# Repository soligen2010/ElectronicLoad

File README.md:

# ElectronicLoad

Here is my DC Load project, inspired by Dave Jones, MJLorton, and Kibi.

I have this on a breadboard and it all seems to be working, but as I am a beginner, I would appreciate any feedback before I start soldering.

I built in an Arduino and 16 bit DAC (ADS1115) to monitor and display volts and amps without a multi meter. It also displays watts, and software enforces max watts. It will turn off the load if the watts or voltage exceeds the software limits.

Several break-out boards are referenced: Arduino Nano, 16x2 LCD, ADS1115, and my own negative 2.5 volt generator. I don’t have the schematic drawn for the -2.5 generator. Basically the PWM drives a totem pole and capacitors/diodes to get the negative voltage, then regulated with a TL431A. Even though the TLC272 is supposed to go to ground, I found it wasn’t very good near ground, so I added the negative. I probably only needed -.5V, but -2.5V is the TL431 reference voltage.

Power is supplied by an old camera battery charger that I hacked into a DC supply. I figure anything at around 9V should work fine. The heat sink fan is the only thing driven directly by the input voltage. Everything else either uses the Arduino’s built in 5V regulator or 7.5V regulated by VR1.

Output from IC1A is split with identical voltage dividers – one to set the input to IC1B and the other goes to the DAC for reading by the Arduino.

Q2 is Arduino controlled and turns the load on or off. R13 ensures the output of IC1B is low when the load is off by pulling the non-inverting input down to about -.6V. The LCD display will show either the “set” amps or the actual amps depending if it is in “set” or “run” mode (controlled by MODE_BUTTON).

Q3 is an HRF3205 that I salvaged from an old UPS. I had started out using an FQP30N06, but I fried several, so went to the HRF3205 which handles a lot more current. The only theory I have for FQP30N06 is the amp surge when the load turns on. I did a re-design to reduce the turn on surge time by making sure IC1B output is LOW when the load is off (Q2 and R13). But I still went with the HRF3205.

Stabilizing the feedback was my biggest challenge. I wish I would have bought an oscilloscope sooner . When I changed to the HRF3205, I had to change C4 from 10n to 100n, added R14 (and R5 for symmetry) and removed the 100R resistor I had between IC1B and Q3. C4 ended up bigger than I expected it should be, and I am a bit uncertain about the lack of a Q3 gate resistor, so comments on this are welcome.

I didn’t fully buffer the inputs to the DAC. When I had put them in, the buffer added error, so I decided to remove them to simplify the circuit and compensate for the low impedance DAC inputs in software. The software will handle all calibration and compensation for any mis-matched component values.

I tested with various amp settings at 3.3ish, 5ish, and 12ish volts using a converted ATX power supply. I also testing the low end with an AA cell that I abusively drained. I’d like to test with some higher voltages to see how it does, but first I’ll need to build something that can go higher than 12V.

 Copyright 2018 by Dennis Cabell
 KE8FZX

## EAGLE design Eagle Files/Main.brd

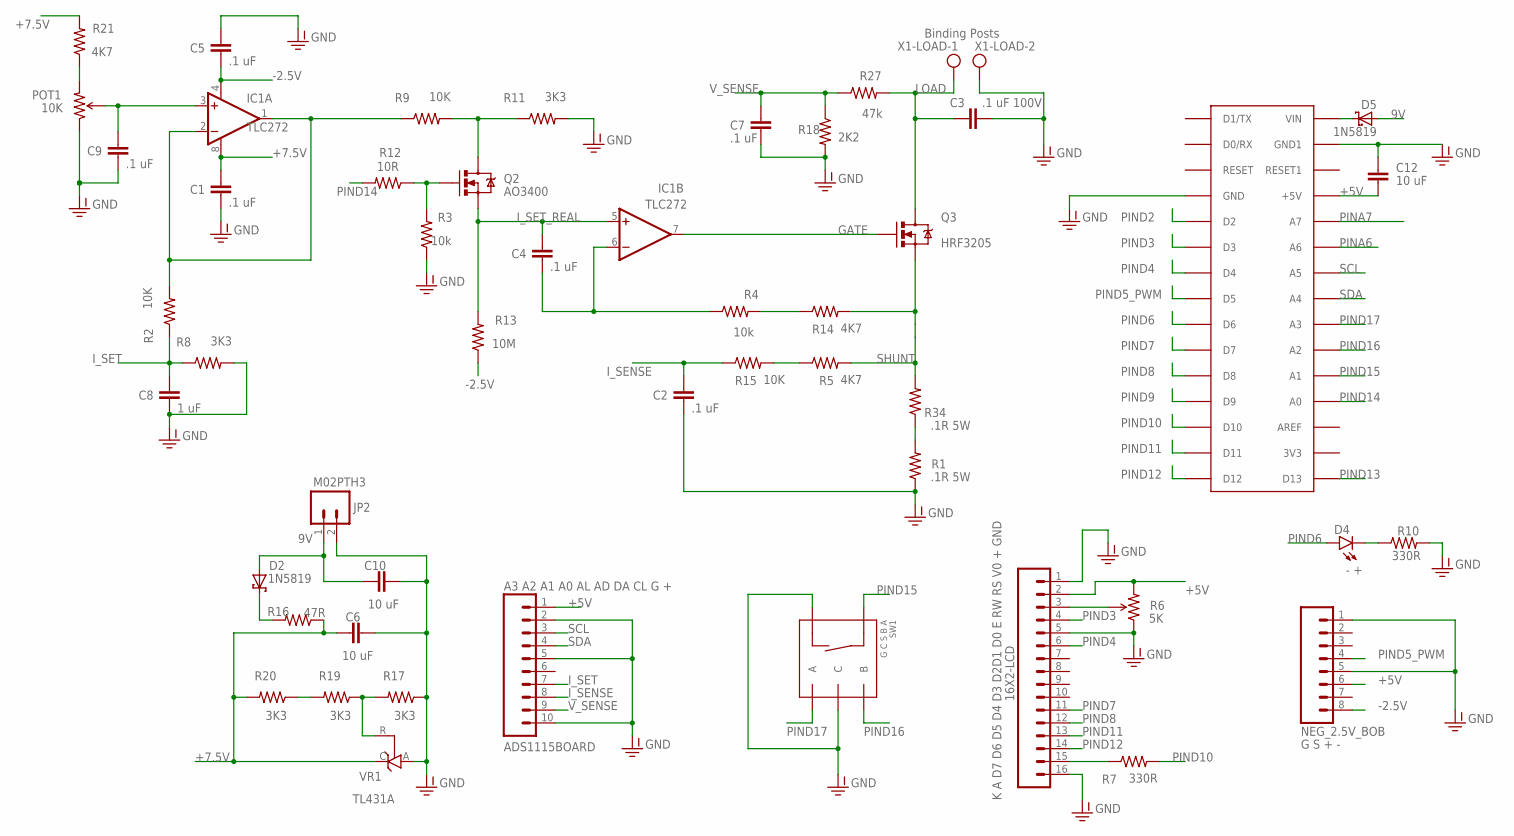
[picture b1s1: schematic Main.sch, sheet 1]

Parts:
16X2-LCD: K A D7 D6 D5 D4 D3 D2D1 D0 E RW RS V0 + GND; 1X16
ADS1115BOARD: A3 A2 A1 A0 AL AD DA CL G +; 1X10_NO_SILK
ARDUINO_NANO: NANO; PDIP-32
C1, C2, C4, C5, C7, C9: .1 uF; CAP-PTH-5MM
C3: .1 uF 100V; CAP-PTH-5MM
C6, C10, C12: 10 uF; CAP-PTH-5MM
C8: 1 uF; CAP-PTH-5MM
D2, D5: 1N5819; DO41-10
D4: - +; LED5MM
IC1: TLC272; DIP08
JP2: M02PTH3; 1X02_LONGPADS
NEG_2.5V_BOB: G S + -; 1X08_ROUND
POT1: 10K; 3386U
Q2: AO3400; SOT23-3
Q3: HRF3205; TO220V
R1, R34: .1R 5W; VTA53
R2, R9: 10K; AXIAL-0.4
R3, R4: 10k; AXIAL-0.4
R5, R14, R21: 4K7; AXIAL-0.4
R6: 5K; TRIM_POT_PTH
R7, R10: 330R; AXIAL-0.4
R8: 3K3; AXIAL-0.5
R11, R17, R19, R20: 3K3; AXIAL-0.4
R12: 10R; AXIAL-0.4
R13: 10M; AXIAL-0.5
R15: 10K; AXIAL-0.5
R16: 47R; AXIAL-0.4
R18: 2K2; AXIAL-0.4
R27: 47k; AXIAL-0.5
SW1: G C S B A; 1X05
VR1: TL431A; TO92-CLP
X1-LOAD: Binding Posts; W237-102

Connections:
9V: C10.1, D2.A, D5.A, JP2.1; also elsewhere on the board
+5V: 16X2-LCD.2, ADS1115BOARD.1, ARDUINO_NANO.+5V, C12.1, NEG_2.5V_BOB.6, R6.3 (CW); also elsewhere on the board
+7.5V: C1.1, C6.1, IC1.8 (V+), R16.P$1 (1), R20.P$2 (2), R21.P$2 (2), VR1.C; also elsewhere on the board
-2.5V: C5.2, IC1.4 (V-), NEG_2.5V_BOB.8, R13.P$1 (1); also elsewhere on the board
GATE: IC1.7 (OUT), Q3.1 (G); also elsewhere on the board
GND-ISO: 16X2-LCD.1, 16X2-LCD.5, 16X2-LCD.16, ADS1115BOARD.2, ADS1115BOARD.5, ADS1115BOARD.10, ARDUINO_NANO.GND, ARDUINO_NANO.GND1, C1.2, C2.2, C3.2, C5.1, C6.2, C7.2, C8.2, C9.2, C10.2, C12.2, JP2.2, NEG_2.5V_BOB.1, NEG_2.5V_BOB.5, POT1.1 (CCW), R1.1, R3.P$1 (1), R6.1 (CCW), R8.P$2 (2), R10.P$2 (2), R11.P$2 (2), R17.P$1 (1), R18.P$2 (2), SW1.1 (SW-), SW1.2 (C), VR1.A, X1-LOAD.2; also elsewhere on the board
I_SENSE: ADS1115BOARD.8, C2.1, R15.P$1 (1)
I_SET: ADS1115BOARD.7, C8.1, R2.P$1 (1), R8.P$1 (1); also elsewhere on the board
I_SET_REAL: C4.1, IC1.5 (+IN), Q2.2 (S), R13.P$2 (2); also elsewhere on the board
LOAD: C3.1, Q3.2 (D), R27.P$2 (2), X1-LOAD.1; also elsewhere on the board
unnamed: R1.2, R34.1
unnamed: 16X2-LCD.15, R7.P$1 (1)
unnamed: R4.P$2 (2), R14.P$1 (1)
unnamed: 16X2-LCD.3, R6.2 (WIPER)
unnamed: C9.1, IC1.3 (+IN), POT1.2 (WIPER)
unnamed: D2.C, R16.P$2 (2)
unnamed: IC1.1 (OUT), IC1.2 (-IN), R2.P$2 (2), R9.P$1 (1)
unnamed: ARDUINO_NANO.VIN, D5.C
unnamed: Q2.3 (D), R9.P$2 (2), R11.P$1 (1)
unnamed: R5.P$1 (1), R15.P$2 (2)
unnamed: Q2.1 (G), R3.P$2 (2), R12.P$1 (1)
unnamed: D4.K (C), R10.P$1 (1)
unnamed: POT1.3 (CW), R21.P$1 (1)
unnamed: R17.P$2 (2), R19.P$1 (1), VR1.R
unnamed: R19.P$2 (2), R20.P$1 (1)
unnamed: C4.2, IC1.6 (-IN), R4.P$1 (1)
PINA6: ARDUINO_NANO.A1 (A6); also elsewhere on the board
PINA7: ARDUINO_NANO.A0 (A7); also elsewhere on the board
PIND2: ARDUINO_NANO.D2; also elsewhere on the board
PIND3: 16X2-LCD.4, ARDUINO_NANO.D3
PIND4: 16X2-LCD.6, ARDUINO_NANO.D4
PIND5_PWM: ARDUINO_NANO.D5, NEG_2.5V_BOB.4
PIND6: ARDUINO_NANO.D6, D4.A
PIND7: 16X2-LCD.11, ARDUINO_NANO.D7
PIND8: 16X2-LCD.12, ARDUINO_NANO.D8
PIND9: ARDUINO_NANO.D9; also elsewhere on the board
PIND10: ARDUINO_NANO.D10, R7.P$2 (2)
PIND11: 16X2-LCD.13, ARDUINO_NANO.D11
PIND12: 16X2-LCD.14, ARDUINO_NANO.D12
PIND13: ARDUINO_NANO.D13; also elsewhere on the board
PIND14: ARDUINO_NANO.A7 (A0), R12.P$2 (2)
PIND15: ARDUINO_NANO.A6 (A1), SW1.3 (SW+)
PIND16: ARDUINO_NANO.A5 (A2), SW1.4 (B)
PIND17: ARDUINO_NANO.A4 (A3), SW1.5 (A)
SCL: ADS1115BOARD.3, ARDUINO_NANO.A2 (A5); also elsewhere on the board
SDA: ADS1115BOARD.4, ARDUINO_NANO.A3 (A4); also elsewhere on the board
SHUNT: Q3.3 (S), R5.P$2 (2), R14.P$2 (2), R34.2; also elsewhere on the board
V_SENSE: ADS1115BOARD.9, C7.1, R18.P$1 (1), R27.P$1 (1)

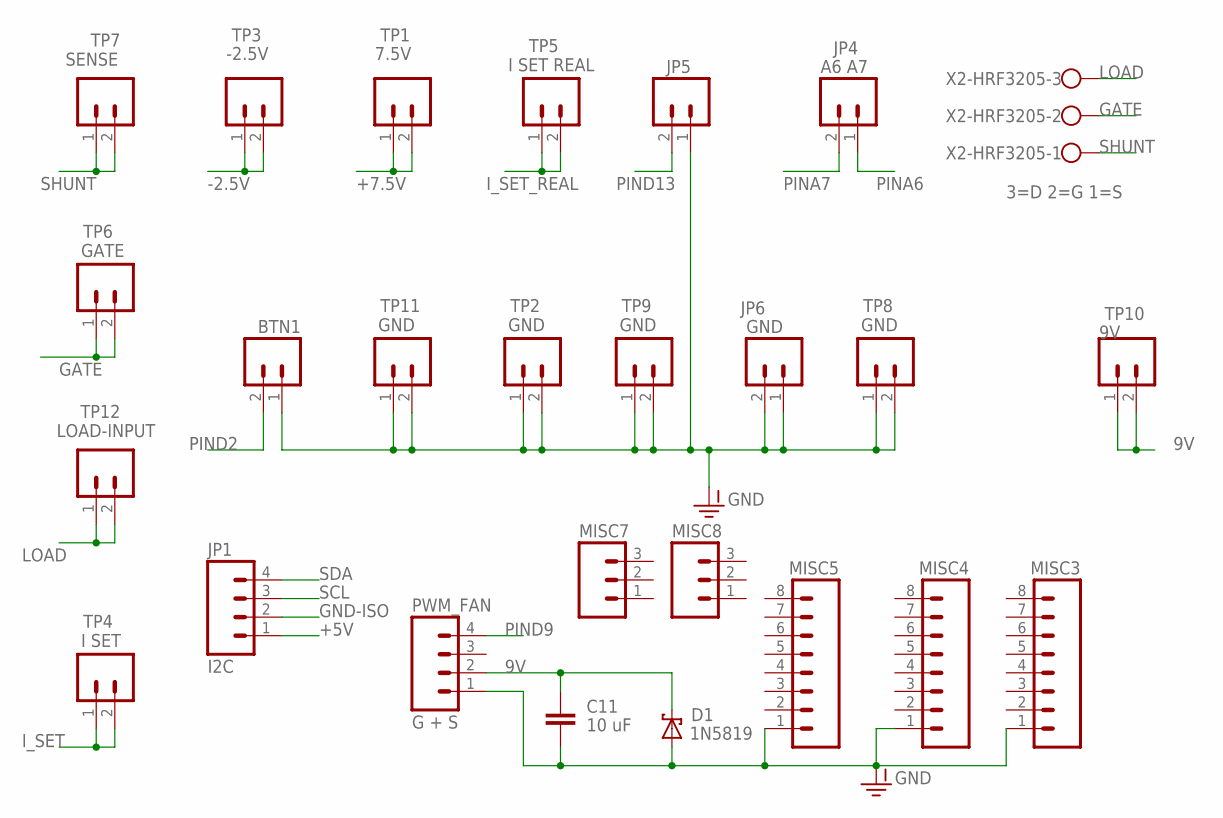
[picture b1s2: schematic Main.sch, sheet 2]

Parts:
BTN1: 1X02
C11: 10 uF; CAP-PTH-5MM
D1: 1N5819; DO41-10
JP1: I2C; 1X04
JP4: A6 A7; 1X02
JP5: 1X02
JP6: GND; 1X02
MISC3, MISC4, MISC5: 1X08_ROUND
MISC7, MISC8: 1X03
PWM_FAN: G + S; 1X04
TP1: 7.5V; 1X02
TP2, TP8, TP9, TP11: GND; 1X02_LONGPADS
TP3: -2.5V; 1X02
TP4: I SET; 1X02_LONGPADS
TP5: I SET REAL; 1X02_LONGPADS
TP6: GATE; 1X02_LONGPADS
TP7: SENSE; 1X02_LONGPADS
TP10: 9V; 1X02
TP12: LOAD-INPUT; 1X02_LONGPADS
X2-HRF3205: 3=D 2=G 1=S; W237-103

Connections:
9V: C11.2, D1.C, PWM_FAN.2, TP10.1, TP10.2; also elsewhere on the board
+5V: JP1.1; also elsewhere on the board
+7.5V: TP1.1, TP1.2; also elsewhere on the board
-2.5V: TP3.1, TP3.2; also elsewhere on the board
GATE: TP6.1, TP6.2, X2-HRF3205.2; also elsewhere on the board
GND-ISO: BTN1.1, C11.1, D1.A, JP1.2, JP5.1, JP6.1, JP6.2, MISC3.1, MISC4.1, MISC5.1, PWM_FAN.1, TP2.1, TP2.2, TP8.1, TP8.2, TP9.1, TP9.2, TP11.1, TP11.2; also elsewhere on the board
I_SET: TP4.1, TP4.2; also elsewhere on the board
I_SET_REAL: TP5.1, TP5.2; also elsewhere on the board
LOAD: TP12.1, TP12.2, X2-HRF3205.3; also elsewhere on the board
PINA6: JP4.1; also elsewhere on the board
PINA7: JP4.2; also elsewhere on the board
PIND2: BTN1.2; also elsewhere on the board
PIND9: PWM_FAN.4; also elsewhere on the board
PIND13: JP5.2; also elsewhere on the board
SCL: JP1.3; also elsewhere on the board
SDA: JP1.4; also elsewhere on the board
SHUNT: TP7.1, TP7.2, X2-HRF3205.1; also elsewhere on the board

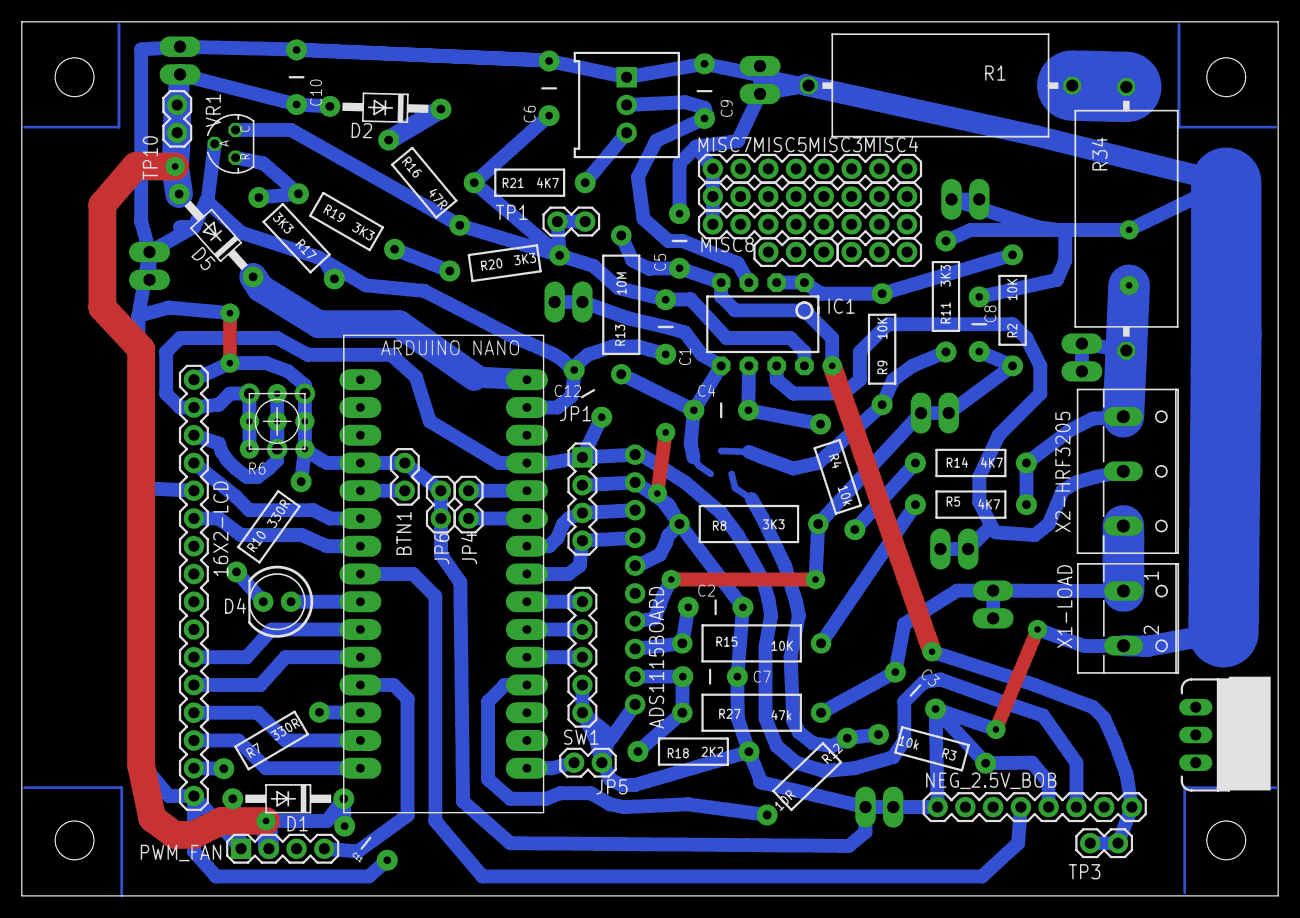
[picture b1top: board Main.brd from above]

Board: 2 copper layers, 115.0 x 80.0 mm, 75 parts (1 on the bottom side), 48 nets.

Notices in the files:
Eagle Files/Main.brd:
Copyright 2016 Dennis Cabell
parts and their libraries:
SparkFun-Connectors: Licensing: Creative Commons ShareAlike 4.0 International - https://creativecommons.org/licenses/by-sa/4.0
